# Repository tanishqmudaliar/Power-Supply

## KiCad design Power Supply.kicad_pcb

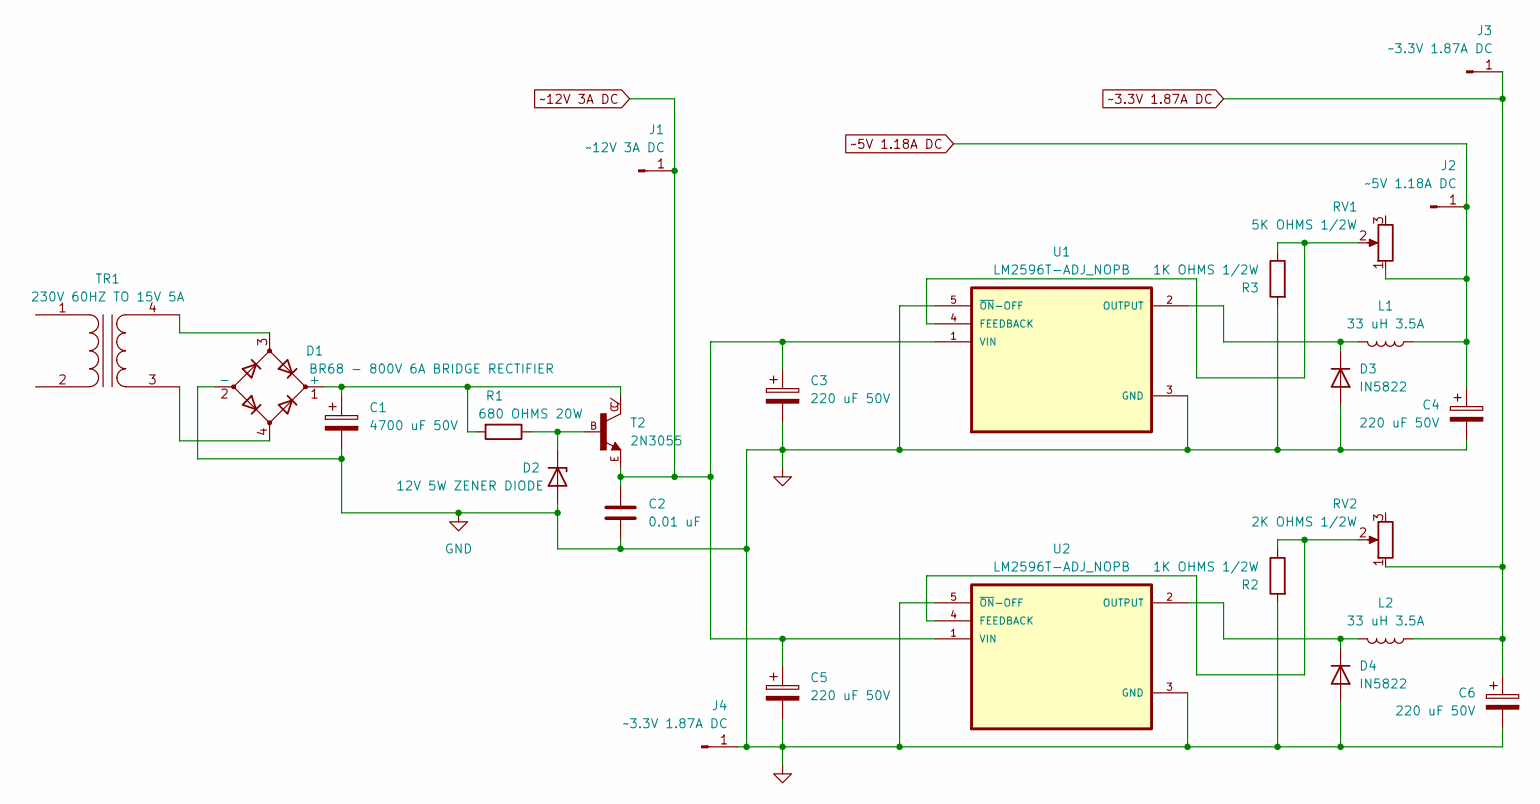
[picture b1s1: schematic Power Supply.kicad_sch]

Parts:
C1: 4700 uF 50V; CP_Radial_D18.0mm_P7.50mm
C2: 0.01 uF; C_Disc_D6.0mm_W2.5mm_P5.00mm
C3, C4, C5, C6: 220 uF 50V; CP_Radial_D10.0mm_P5.00mm
D1: BR68 - 800V 6A BRIDGE RECTIFIER; BR68
D2: 12V 5W ZENER DIODE; DIOAD1543W101L863D368
D3, D4: IN5822; D_DO-201AD_P15.24mm_Horizontal
J1: ~12V 3A DC; Banana Clips
J2: ~5V 1.18A DC; Banana Clips
J3, J4: ~3.3V 1.87A DC; Banana Clips
L1, L2: 33 uH 3.5A; L_Toroid_Vertical_L16.3mm_W7.1mm_P7.11mm_Pulse_H
R1: 680 OHMS 20W; R_Axial_Power_L50.0mm_W9.0mm_P60.96mm
R2, R3: 1K OHMS 1/2W; R_Axial_DIN0309_L9.0mm_D3.2mm_P12.70mm_Horizontal
RV1: 5K OHMS 1/2W; Potentiometer_Runtron_RM-065_Vertical
RV2: 2K OHMS 1/2W; Potentiometer_Runtron_RM-065_Vertical
T2: 2N3055; TO3
TR1: 230V 60HZ TO 15V 5A; 15V 5A Transformer
U1, U2: LM2596T-ADJ_NOPB; TO170P1016X470X2092-5

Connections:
GND: C1.2, C2.2, C3.2, C4.2, C5.2, C6.2, D1.2 (-), D2.2 (A), D3.2 (A), D4.2 (A), J4.1, R2.2, R3.2, U1.3 (GND), U1.5 (~ON-OFF), U2.3 (GND), U2.5 (~ON-OFF)
unnamed: C1.1, D1.1 (+), R1.2, T2.C, T2.C/
unnamed: D2.1 (K), R1.1, T2.B
unnamed: D3.1 (K), L1.2, U1.2 (OUTPUT)
unnamed: D4.1 (K), L2.2, U2.2 (OUTPUT)
unnamed: D1.4, TR1.3 (SA)
unnamed: D1.3, TR1.4 (SB)
unnamed: R3.1, RV1.2, U1.4 (FEEDBACK)
unnamed: R2.1, RV2.2, U2.4 (FEEDBACK)
~3.3V 1.87A DC: C6.1, J3.1, L2.1, RV2.1
~5V 1.18A DC: C4.1, J2.1, L1.1, RV1.1
~12V 3A DC: C2.1, C3.1, C5.1, J1.1, T2.E, U1.1 (VIN), U2.1 (VIN)

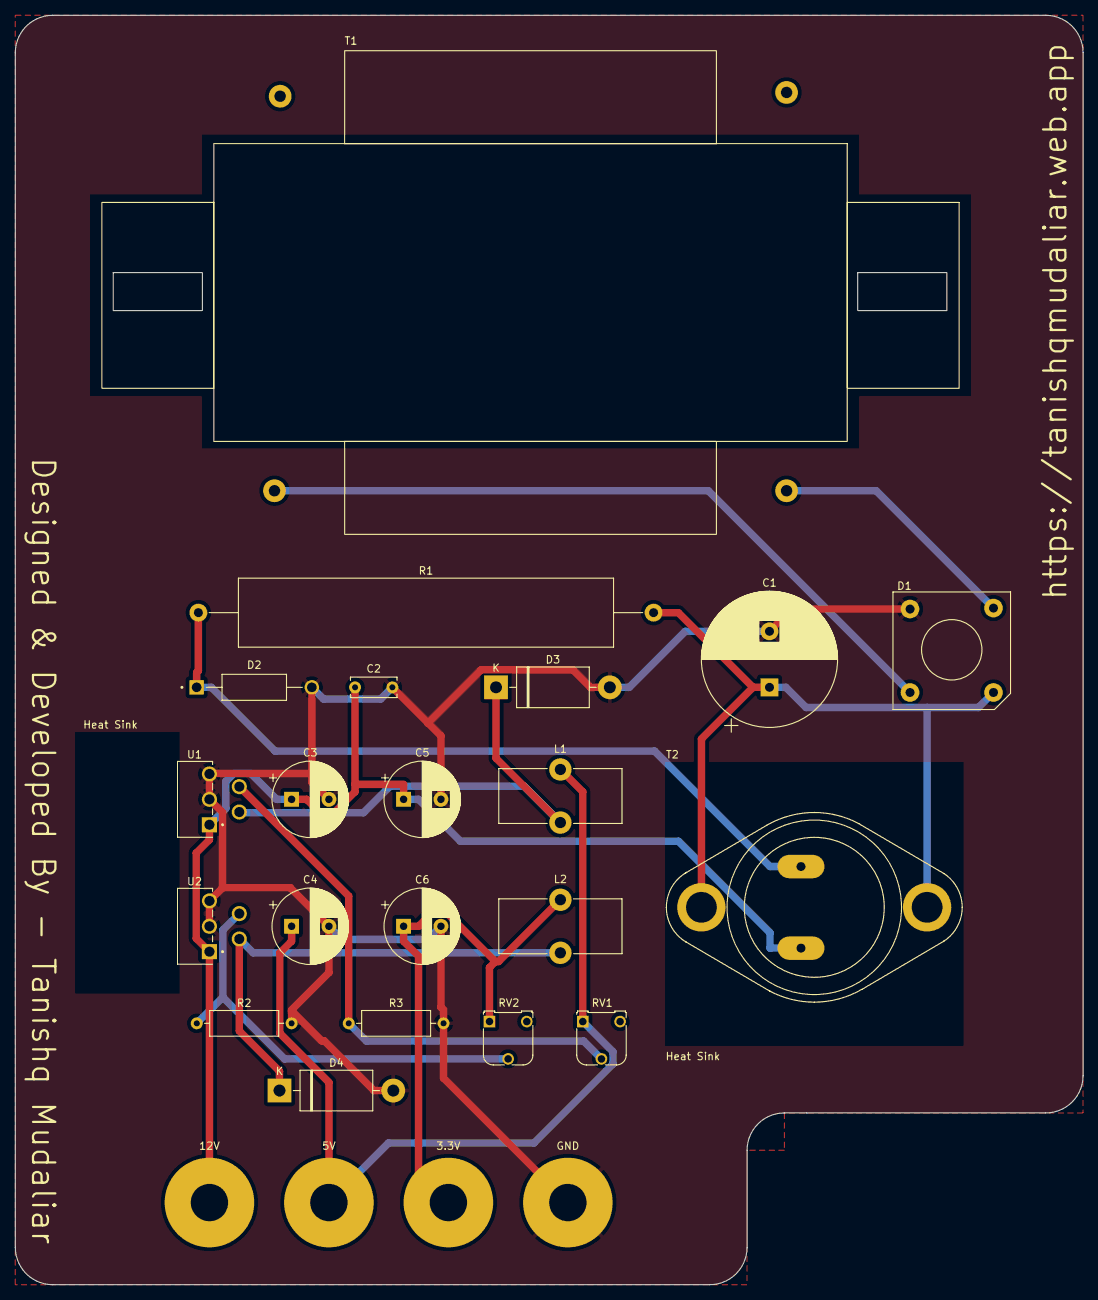
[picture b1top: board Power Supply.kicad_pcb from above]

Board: 2 copper layers, 143.0 x 170.0 mm, 25 parts (0 on the bottom side), 12 nets.

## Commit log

2023-12-19 master
